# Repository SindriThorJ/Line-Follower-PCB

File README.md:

This repo is for storing the design files of my PCB based IR line follower, the line follower can have multiple I2C addresses by modifying the solder bridges according to the table on the silkscreen.

Raytraced front view:

Raytraced back view:

Actual picture of the board:

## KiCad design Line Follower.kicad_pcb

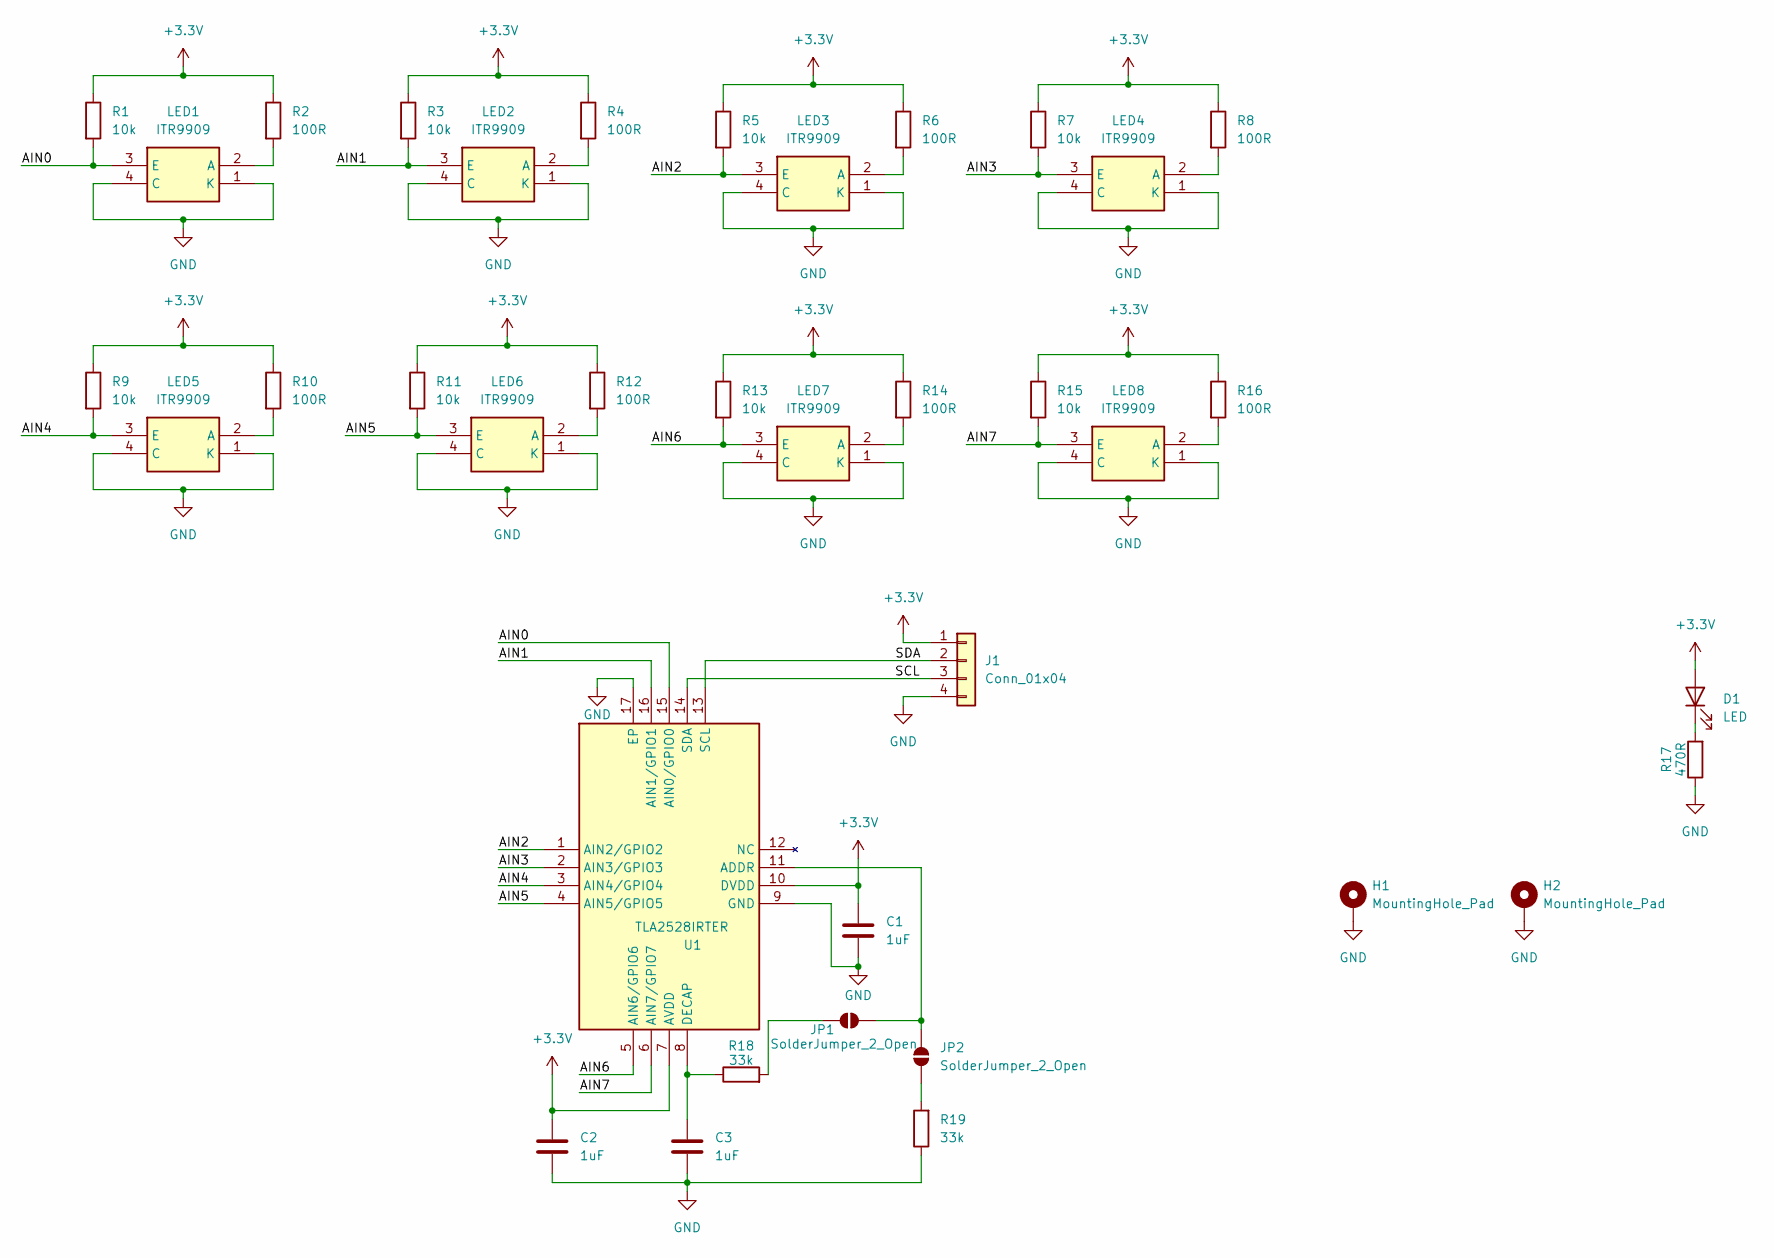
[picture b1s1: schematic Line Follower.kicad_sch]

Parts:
C1, C2, C3: 1uF; C_0603_1608Metric
D1: LED; LED_0603_1608Metric
H1, H2: MountingHole_Pad; MountingHole_3.2mm_M3_Pad_Via
J1: Conn_01x04; JST_XH_S4B-XH-A-1_1x04_P2.50mm_Horizontal
JP1, JP2: SolderJumper_2_Open; SolderJumper-2_P1.3mm_Open_RoundedPad1.0x1.5mm
LED1, LED2, LED3, LED4, LED5, LED6, LED7, LED8: ITR9909; Manufacturer_Part_Number ITR9909
R1, R3, R5, R7, R9, R11, R13, R15: 10k; R_0603_1608Metric
R2, R4, R6, R8, R10, R12, R14, R16: 100R; R_0603_1608Metric
R17: 470R; R_0603_1608Metric
R18, R19: 33k; R_0603_1608Metric
U1: TLA2528IRTER; QFN50P300X300X80-17N-D; Manufacturer_Part_Number TLA2528IRTER; Mouser Part Number 595-TLA2528IRTER

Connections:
+3.3V: C1.1, C2.1, D1.2 (A), J1.1, R1.1, R2.1, R3.1, R4.1, R5.1, R6.1, R7.1, R8.1, R9.1, R10.1, R11.1, R12.1, R13.1, R14.1, R15.1, R16.1, U1.7 (AVDD), U1.10 (DVDD)
/AIN0: LED1.3 (E), R1.2, U1.15 (AIN0/GPIO0)
/AIN1: LED2.3 (E), R3.2, U1.16 (AIN1/GPIO1)
/AIN2: LED3.3 (E), R5.2, U1.1 (AIN2/GPIO2)
/AIN3: LED4.3 (E), R7.2, U1.2 (AIN3/GPIO3)
/AIN4: LED5.3 (E), R9.2, U1.3 (AIN4/GPIO4)
/AIN5: LED6.3 (E), R11.2, U1.4 (AIN5/GPIO5)
/AIN6: LED7.3 (E), R13.2, U1.5 (AIN6/GPIO6)
/AIN7: LED8.3 (E), R15.2, U1.6 (AIN7/GPIO7)
/SCL: J1.3, U1.14 (SDA)
/SDA: J1.2, U1.13 (SCL)
GND: C1.2, C2.2, C3.2, H1.1, H2.1, J1.4, LED1.1 (K), LED1.4 (C), LED2.1 (K), LED2.4 (C), LED3.1 (K), LED3.4 (C), LED4.1 (K), LED4.4 (C), LED5.1 (K), LED5.4 (C), LED6.1 (K), LED6.4 (C), LED7.1 (K), LED7.4 (C), LED8.1 (K), LED8.4 (C), R17.1, R19.1, U1.9 (GND), U1.17 (EP)
unnamed: D1.1 (K), R17.2
unnamed: JP1.1 (A), JP2.2 (B), U1.11 (ADDR)
unnamed: JP1.2 (B), R18.2
unnamed: JP2.1 (A), R19.2
unnamed: LED1.2 (A), R2.2
unnamed: LED2.2 (A), R4.2
unnamed: LED3.2 (A), R6.2
unnamed: LED4.2 (A), R8.2
unnamed: LED5.2 (A), R10.2
unnamed: LED6.2 (A), R12.2
unnamed: LED7.2 (A), R14.2
unnamed: LED8.2 (A), R16.2
unnamed: C3.1, R18.1, U1.8 (DECAP)

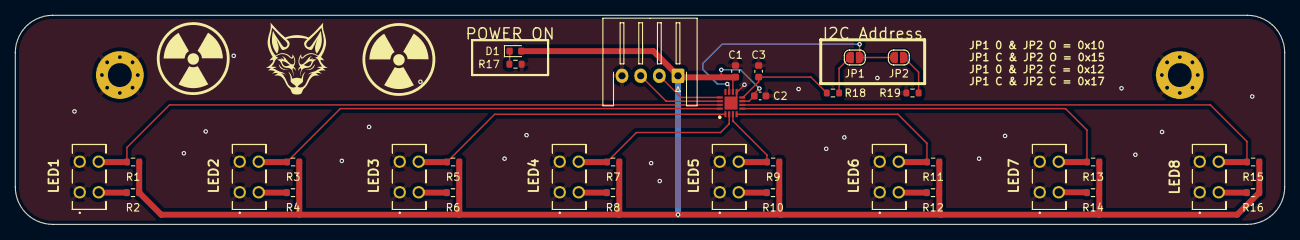
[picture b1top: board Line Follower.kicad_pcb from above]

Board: 2 copper layers, 170.0 x 28.0 mm, 37 parts (0 on the bottom side), 25 nets.

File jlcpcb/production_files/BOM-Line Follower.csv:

Comment,Designator,Footprint,LCSC
Conn_01x04,,JST_XH_S4B-XH-A-1_1x04_P2.50mm_Horizontal,C157925
1uF,"C1,C2,C3",C_0603_1608Metric,C15849
100R,"R10,R12,R14,R16,R2,R4,R6,R8",R_0603_1608Metric,C22775
LED,D1,LED_0603_1608Metric,C2286
470R,R17,R_0603_1608Metric,C23179
10k,"R1,R11,R13,R15,R3,R5,R7,R9",R_0603_1608Metric,C25804
TLA2528IRTER,U1,QFN50P300X300X80-17N-D,C2866175
33k,R18,R_0603_1608Metric,C31850
33k,R19,R_0603_1608Metric,C4216
ITR9909,"LED2,LED4,LED6,LED8",ITR9909,C53399

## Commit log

2025-01-28 PCB ordered from JLCPCB
2025-03-11 Added images..
2025-03-11 Added image of the actual board.
2025-03-11 Removed useless backup files
2025-03-11 Create README.md
    Added a readme
